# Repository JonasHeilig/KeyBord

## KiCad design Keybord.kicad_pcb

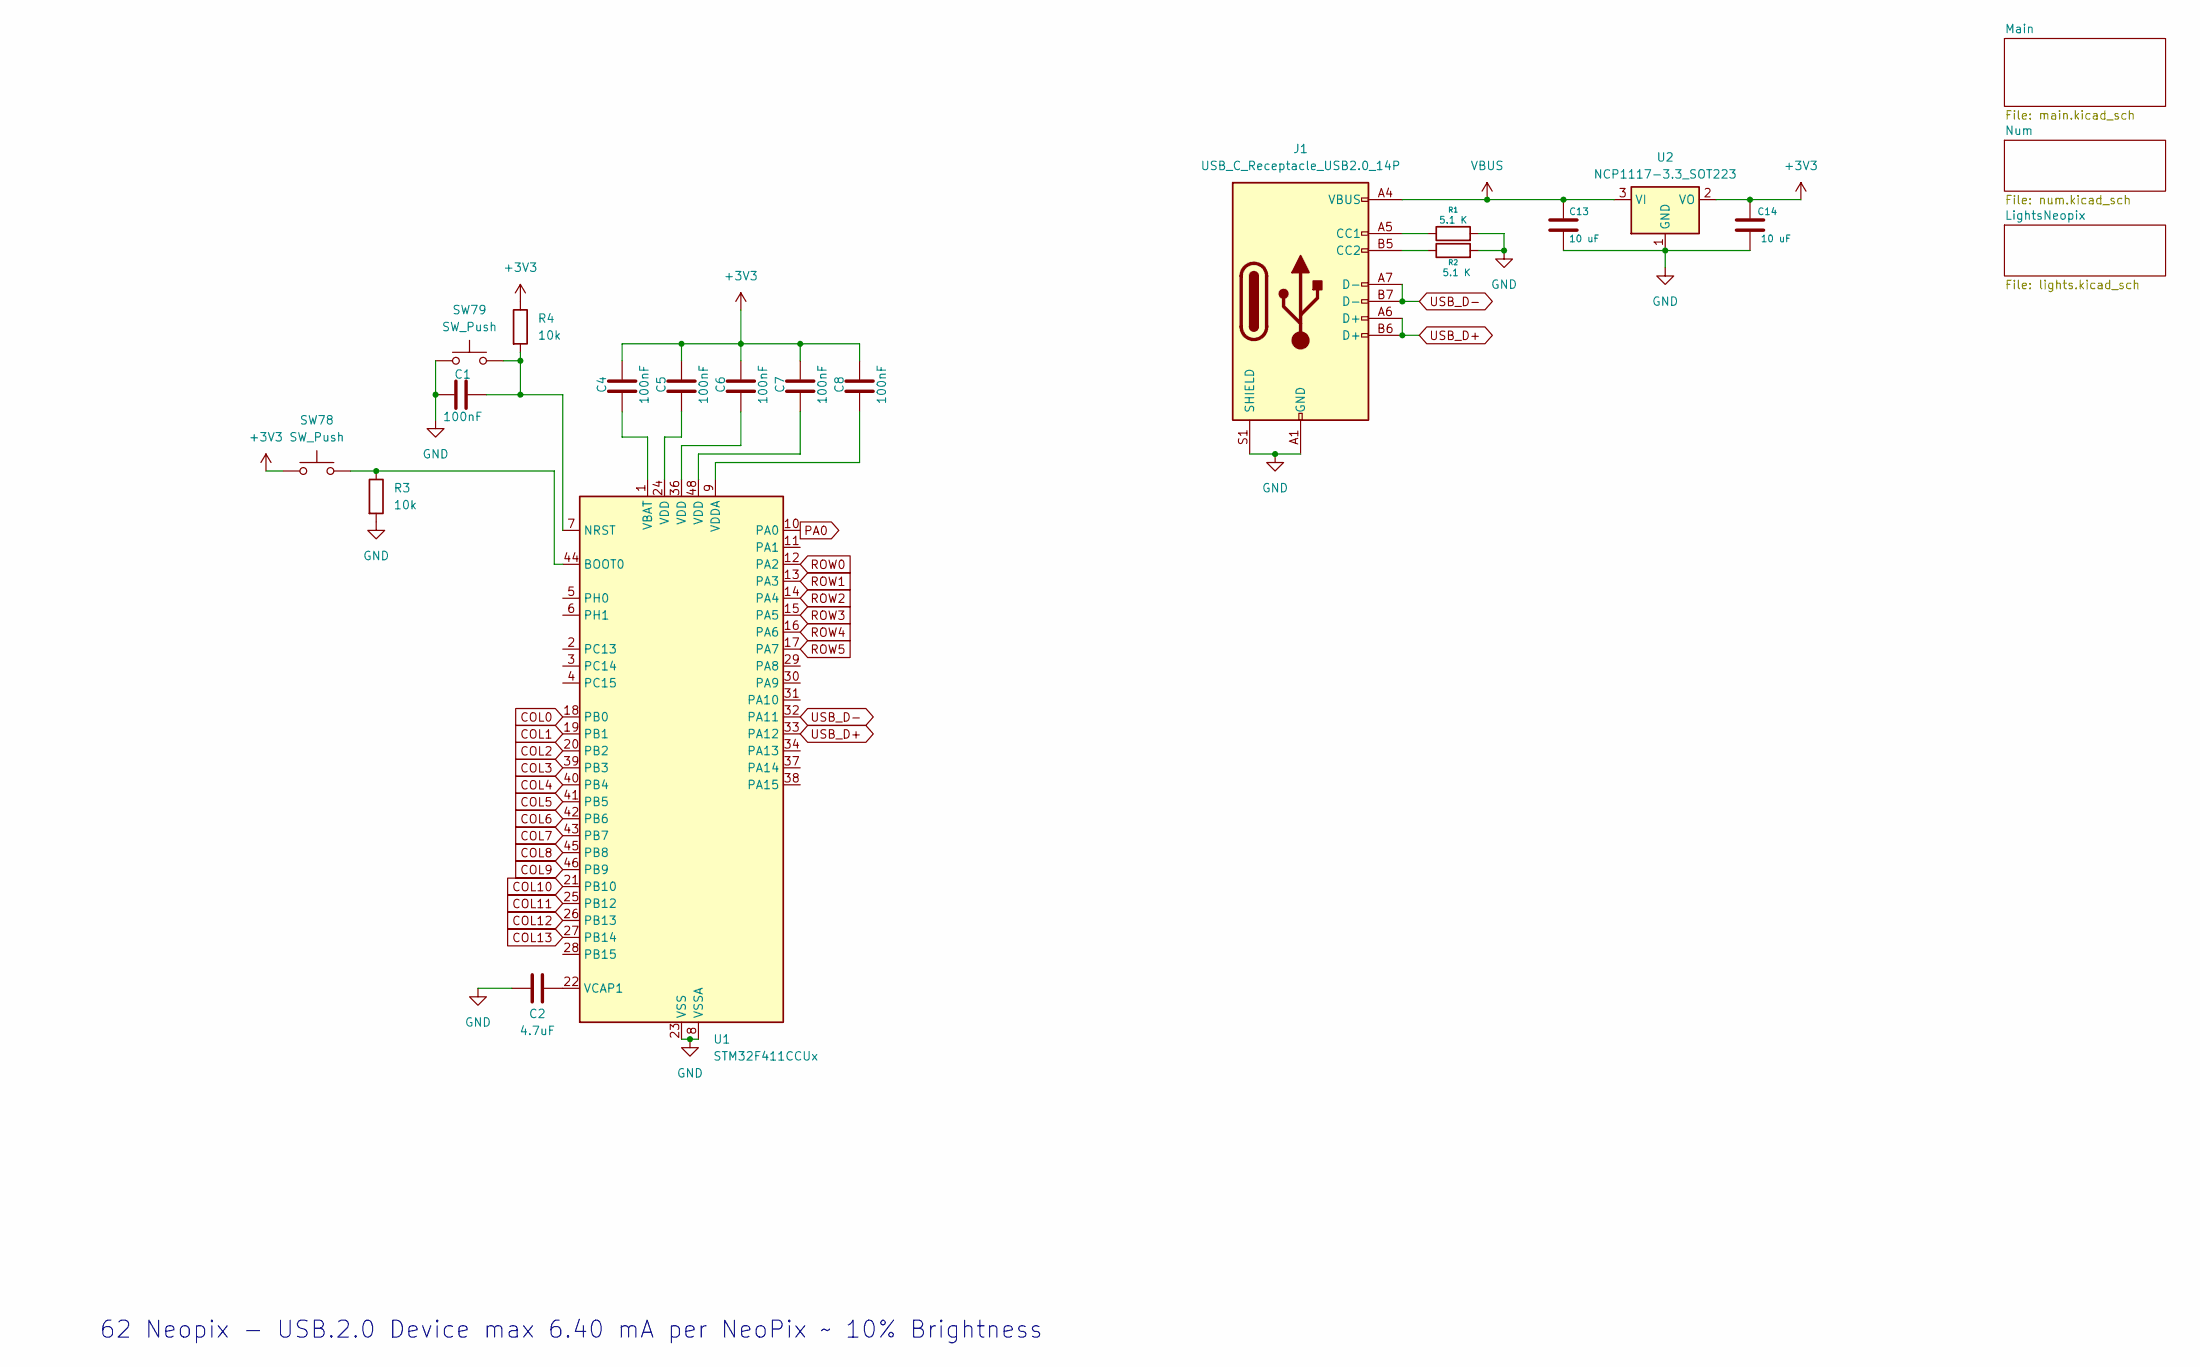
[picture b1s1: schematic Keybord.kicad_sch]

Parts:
C1, C4, C5, C6, C7, C8: 100nF; C_0603_1608Metric
C2: 4.7uF; C_0805_2012Metric
C13, C14: 10 uF; C_0805_2012Metric
J1: USB_C_Receptacle_USB2.0_14P; USB_C_Receptacle_HRO_TYPE-C-31-M-12
R1, R2: 5.1 K; R_0402_1005Metric
R3, R4: 10k; R_0603_1608Metric
SW78, SW79: SW_Push; smd_switch_sunrom4388
U1: STM32F411CCUx; QFN-48-1EP_7x7mm_P0.5mm_EP5.6x5.6mm
U2: NCP1117-3.3_SOT223; SOT-223-3_TabPin2

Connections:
+3V3: C4.2, C5.2, C6.2, C7.2, C8.2, C14.1, R4.1, SW78.1, U2.2 (VO)
COL0: U1.18 (PB0); also elsewhere on the board
COL1: U1.19 (PB1); also elsewhere on the board
COL2: U1.20 (PB2); also elsewhere on the board
COL3: U1.39 (PB3); also elsewhere on the board
COL4: U1.40 (PB4); also elsewhere on the board
COL5: U1.41 (PB5); also elsewhere on the board
COL6: U1.42 (PB6); also elsewhere on the board
COL7: U1.43 (PB7); also elsewhere on the board
COL8: U1.45 (PB8); also elsewhere on the board
COL9: U1.46 (PB9); also elsewhere on the board
COL10: U1.21 (PB10); also elsewhere on the board
COL11: U1.25 (PB12); also elsewhere on the board
COL12: U1.26 (PB13); also elsewhere on the board
COL13: U1.27 (PB14); also elsewhere on the board
GND: C1.1, C2.2, C13.2, C14.2, J1.A1 (GND), J1.A12 (GND), J1.B1 (GND), J1.B12 (GND), J1.S1 (SHIELD), R1.2, R2.2, R3.2, SW79.1, U1.8 (VSSA), U1.23 (VSS), U1.35 (VSS), U1.47 (VSS), U1.49 (VSS), U2.1 (GND); also elsewhere on the board
unnamed: C5.1, U1.24 (VDD)
unnamed: C6.1, U1.36 (VDD)
unnamed: C7.1, U1.48 (VDD)
unnamed: J1.A5 (CC1), R1.1
unnamed: J1.B5 (CC2), R2.1
unnamed: R3.1, SW78.2, U1.44 (BOOT0)
unnamed: C1.2, R4.2, SW79.2, U1.7 (NRST)
unnamed: C4.1, U1.1 (VBAT)
unnamed: C2.1, U1.22 (VCAP1)
unnamed: C8.1, U1.9 (VDDA)
PA0: U1.10 (PA0); also elsewhere on the board
ROW0: U1.12 (PA2); also elsewhere on the board
ROW1: U1.13 (PA3); also elsewhere on the board
ROW2: U1.14 (PA4); also elsewhere on the board
ROW3: U1.15 (PA5); also elsewhere on the board
ROW4: U1.16 (PA6); also elsewhere on the board
ROW5: U1.17 (PA7); also elsewhere on the board
USB_D+: J1.A6 (D+), J1.B6 (D+), U1.33 (PA12)
USB_D-: J1.A7 (D-), J1.B7 (D-), U1.32 (PA11)
VBUS: C13.1, J1.A4 (VBUS), J1.A9 (VBUS), J1.B4 (VBUS), J1.B9 (VBUS), U2.3 (VI); also elsewhere on the board

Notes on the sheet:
62 Neopix - USB.2.0 Device max 6.40 mA per NeoPix ~ 10% Brightness

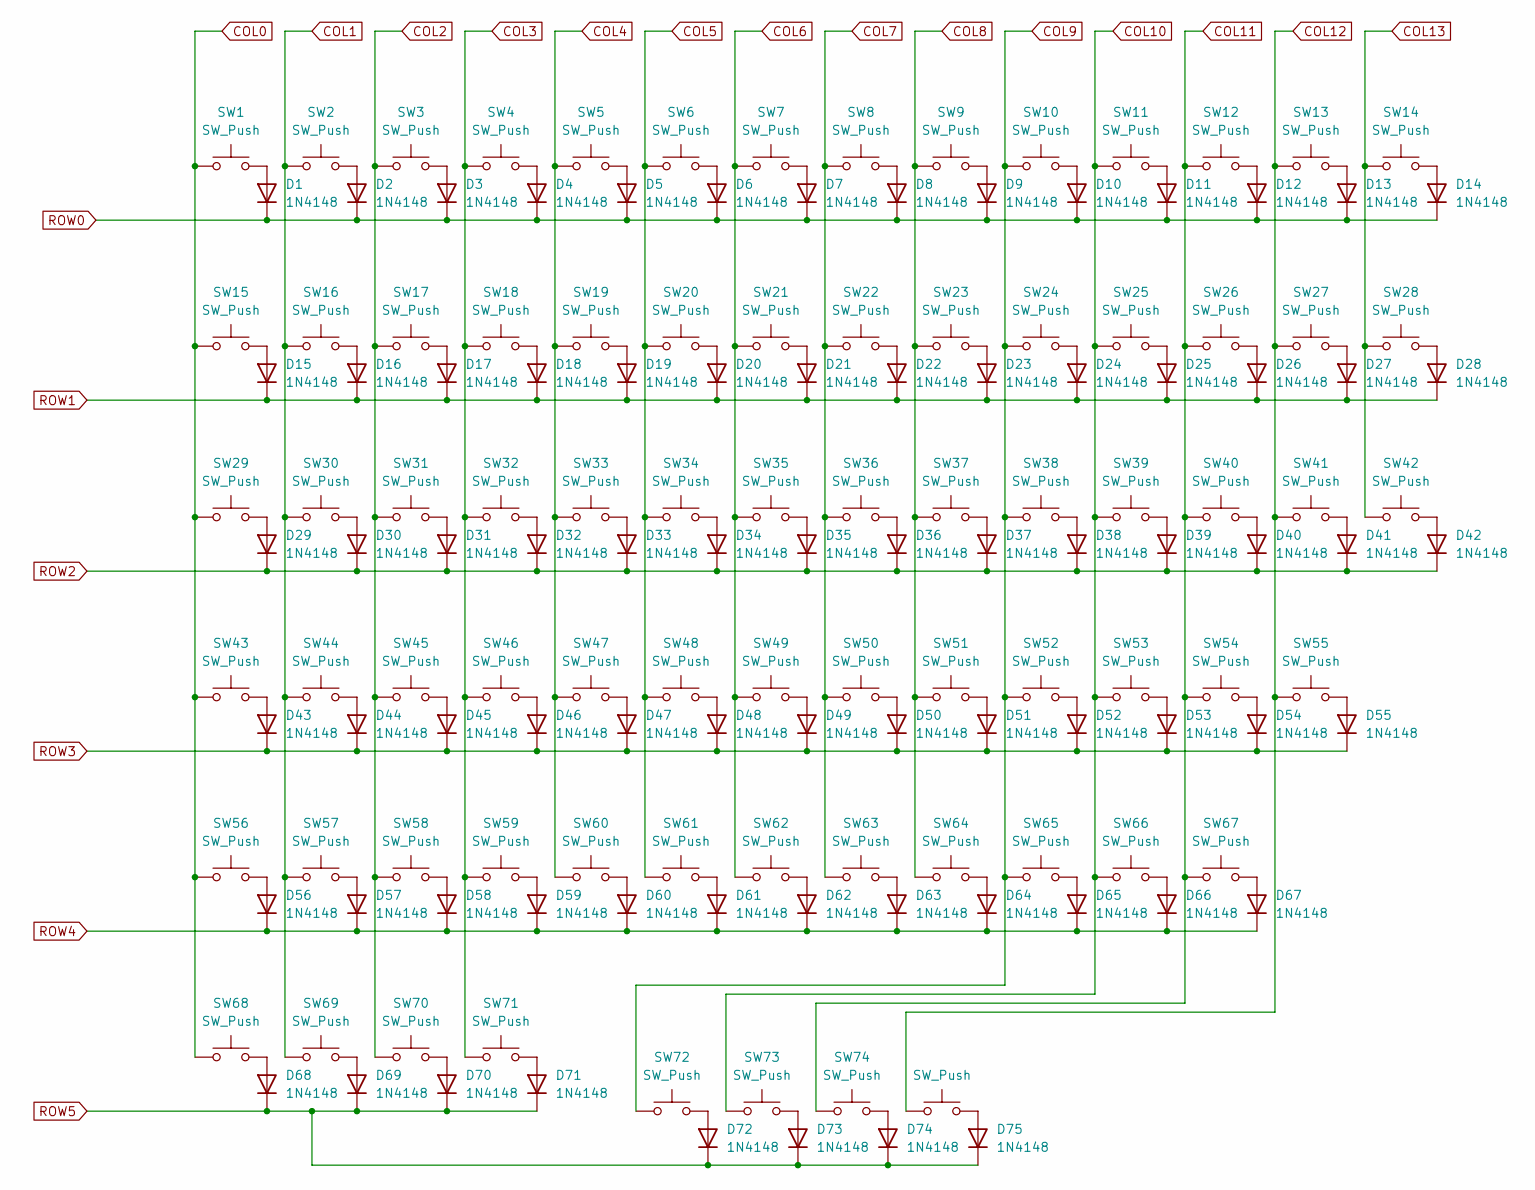
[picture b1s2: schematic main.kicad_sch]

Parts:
D1, D2, D3, D4, D5, D6, D7, D8, D9, D10, D11, D12, D13, D14, D15, D16, D17, D18, D19, D20, D21, D22, D23, D24, D25, D26, D27, D28, D29, D30, D31, D32, D33, D34, D35, D36, D37, D38, D39, D40, D41, D42, D43, D44, D45, D46, D47, D48, D49, D50, D51, D52, D53, D54, D55, D56, D57, D58, D59, D60, D61, D62, D63, D64, D65, D66, D67, D68, D69, D70, D71, D72, D73, D74, D75: 1N4148; D_SOD-123
SW1, SW2, SW3, SW4, SW5, SW6, SW7, SW8, SW9, SW10, SW11, SW12, SW13, SW14, SW15, SW16, SW17, SW18, SW19, SW20, SW21, SW22, SW23, SW24, SW25, SW26, SW27, SW28, SW29, SW30, SW31, SW32, SW33, SW34, SW35, SW36, SW37, SW38, SW39, SW40, SW41, SW42, SW43, SW44, SW45, SW46, SW47, SW48, SW49, SW50, SW51, SW52, SW53, SW54, SW55, SW56, SW57, SW58, SW59, SW60, SW61, SW62, SW63, SW64, SW65, SW66, SW67, SW68, SW69, SW70, SW71, SW72, SW73, SW74, SW75: SW_Push; MX100H

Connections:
COL0: SW1.1, SW15.1, SW29.1, SW43.1, SW56.1, SW68.1; also elsewhere on the board
COL1: SW2.1, SW16.1, SW30.1, SW44.1, SW57.1, SW69.1; also elsewhere on the board
COL2: SW3.1, SW17.1, SW31.1, SW45.1, SW58.1, SW70.1; also elsewhere on the board
COL3: SW4.1, SW18.1, SW32.1, SW46.1, SW59.1, SW71.1; also elsewhere on the board
COL4: SW5.1, SW19.1, SW33.1, SW47.1, SW60.1; also elsewhere on the board
COL5: SW6.1, SW20.1, SW34.1, SW48.1, SW61.1; also elsewhere on the board
COL6: SW7.1, SW21.1, SW35.1, SW49.1, SW62.1; also elsewhere on the board
COL7: SW8.1, SW22.1, SW36.1, SW50.1, SW63.1; also elsewhere on the board
COL8: SW9.1, SW23.1, SW37.1, SW51.1, SW64.1; also elsewhere on the board
COL9: SW10.1, SW24.1, SW38.1, SW52.1, SW65.1, SW72.1; also elsewhere on the board
COL10: SW11.1, SW25.1, SW39.1, SW53.1, SW66.1, SW73.1; also elsewhere on the board
COL11: SW12.1, SW26.1, SW40.1, SW54.1, SW67.1, SW74.1; also elsewhere on the board
COL12: SW13.1, SW27.1, SW41.1, SW55.1, SW75.1; also elsewhere on the board
COL13: SW14.1, SW28.1, SW42.1; also elsewhere on the board
unnamed: D1.2 (A), SW1.2
unnamed: D2.2 (A), SW2.2
unnamed: D3.2 (A), SW3.2
unnamed: D4.2 (A), SW4.2
unnamed: D5.2 (A), SW5.2
unnamed: D6.2 (A), SW6.2
unnamed: D7.2 (A), SW7.2
unnamed: D8.2 (A), SW8.2
unnamed: D9.2 (A), SW9.2
unnamed: D10.2 (A), SW10.2
unnamed: D11.2 (A), SW11.2
unnamed: D12.2 (A), SW12.2
unnamed: D13.2 (A), SW13.2
unnamed: D14.2 (A), SW14.2
unnamed: D15.2 (A), SW15.2
unnamed: D16.2 (A), SW16.2
unnamed: D17.2 (A), SW17.2
unnamed: D18.2 (A), SW18.2
unnamed: D19.2 (A), SW19.2
unnamed: D20.2 (A), SW20.2
unnamed: D21.2 (A), SW21.2
unnamed: D22.2 (A), SW22.2
unnamed: D23.2 (A), SW23.2
unnamed: D24.2 (A), SW24.2
unnamed: D25.2 (A), SW25.2
unnamed: D26.2 (A), SW26.2
unnamed: D27.2 (A), SW27.2
unnamed: D28.2 (A), SW28.2
unnamed: D29.2 (A), SW29.2
unnamed: D30.2 (A), SW30.2
unnamed: D31.2 (A), SW31.2
unnamed: D32.2 (A), SW32.2
unnamed: D33.2 (A), SW33.2
unnamed: D34.2 (A), SW34.2
unnamed: D35.2 (A), SW35.2
unnamed: D36.2 (A), SW36.2
unnamed: D37.2 (A), SW37.2
unnamed: D38.2 (A), SW38.2
unnamed: D39.2 (A), SW39.2
unnamed: D40.2 (A), SW40.2
unnamed: D41.2 (A), SW41.2
unnamed: D42.2 (A), SW42.2
unnamed: D43.2 (A), SW43.2
unnamed: D44.2 (A), SW44.2
unnamed: D45.2 (A), SW45.2
unnamed: D46.2 (A), SW46.2
unnamed: D47.2 (A), SW47.2
unnamed: D48.2 (A), SW48.2
unnamed: D49.2 (A), SW49.2
unnamed: D50.2 (A), SW50.2
unnamed: D51.2 (A), SW51.2
unnamed: D52.2 (A), SW52.2
unnamed: D53.2 (A), SW53.2
unnamed: D54.2 (A), SW54.2
unnamed: D55.2 (A), SW55.2
unnamed: D56.2 (A), SW56.2
unnamed: D57.2 (A), SW57.2
unnamed: D58.2 (A), SW58.2
unnamed: D59.2 (A), SW59.2
unnamed: D60.2 (A), SW60.2
unnamed: D61.2 (A), SW61.2
unnamed: D62.2 (A), SW62.2
unnamed: D63.2 (A), SW63.2
unnamed: D64.2 (A), SW64.2
unnamed: D65.2 (A), SW65.2
unnamed: D66.2 (A), SW66.2
unnamed: D67.2 (A), SW67.2
unnamed: D68.2 (A), SW68.2
unnamed: D69.2 (A), SW69.2
unnamed: D70.2 (A), SW70.2
unnamed: D71.2 (A), SW71.2
unnamed: D72.2 (A), SW72.2
unnamed: D73.2 (A), SW73.2
unnamed: D74.2 (A), SW74.2
unnamed: D75.2 (A), SW75.2
ROW0: D1.1 (K), D2.1 (K), D3.1 (K), D4.1 (K), D5.1 (K), D6.1 (K), D7.1 (K), D8.1 (K), D9.1 (K), D10.1 (K), D11.1 (K), D12.1 (K), D13.1 (K), D14.1 (K); also elsewhere on the board
ROW1: D15.1 (K), D16.1 (K), D17.1 (K), D18.1 (K), D19.1 (K), D20.1 (K), D21.1 (K), D22.1 (K), D23.1 (K), D24.1 (K), D25.1 (K), D26.1 (K), D27.1 (K), D28.1 (K); also elsewhere on the board
ROW2: D29.1 (K), D30.1 (K), D31.1 (K), D32.1 (K), D33.1 (K), D34.1 (K), D35.1 (K), D36.1 (K), D37.1 (K), D38.1 (K), D39.1 (K), D40.1 (K), D41.1 (K), D42.1 (K); also elsewhere on the board
ROW3: D43.1 (K), D44.1 (K), D45.1 (K), D46.1 (K), D47.1 (K), D48.1 (K), D49.1 (K), D50.1 (K), D51.1 (K), D52.1 (K), D53.1 (K), D54.1 (K), D55.1 (K); also elsewhere on the board
ROW4: D56.1 (K), D57.1 (K), D58.1 (K), D59.1 (K), D60.1 (K), D61.1 (K), D62.1 (K), D63.1 (K), D64.1 (K), D65.1 (K), D66.1 (K), D67.1 (K); also elsewhere on the board
ROW5: D68.1 (K), D69.1 (K), D70.1 (K), D71.1 (K), D72.1 (K), D73.1 (K), D74.1 (K), D75.1 (K); also elsewhere on the board

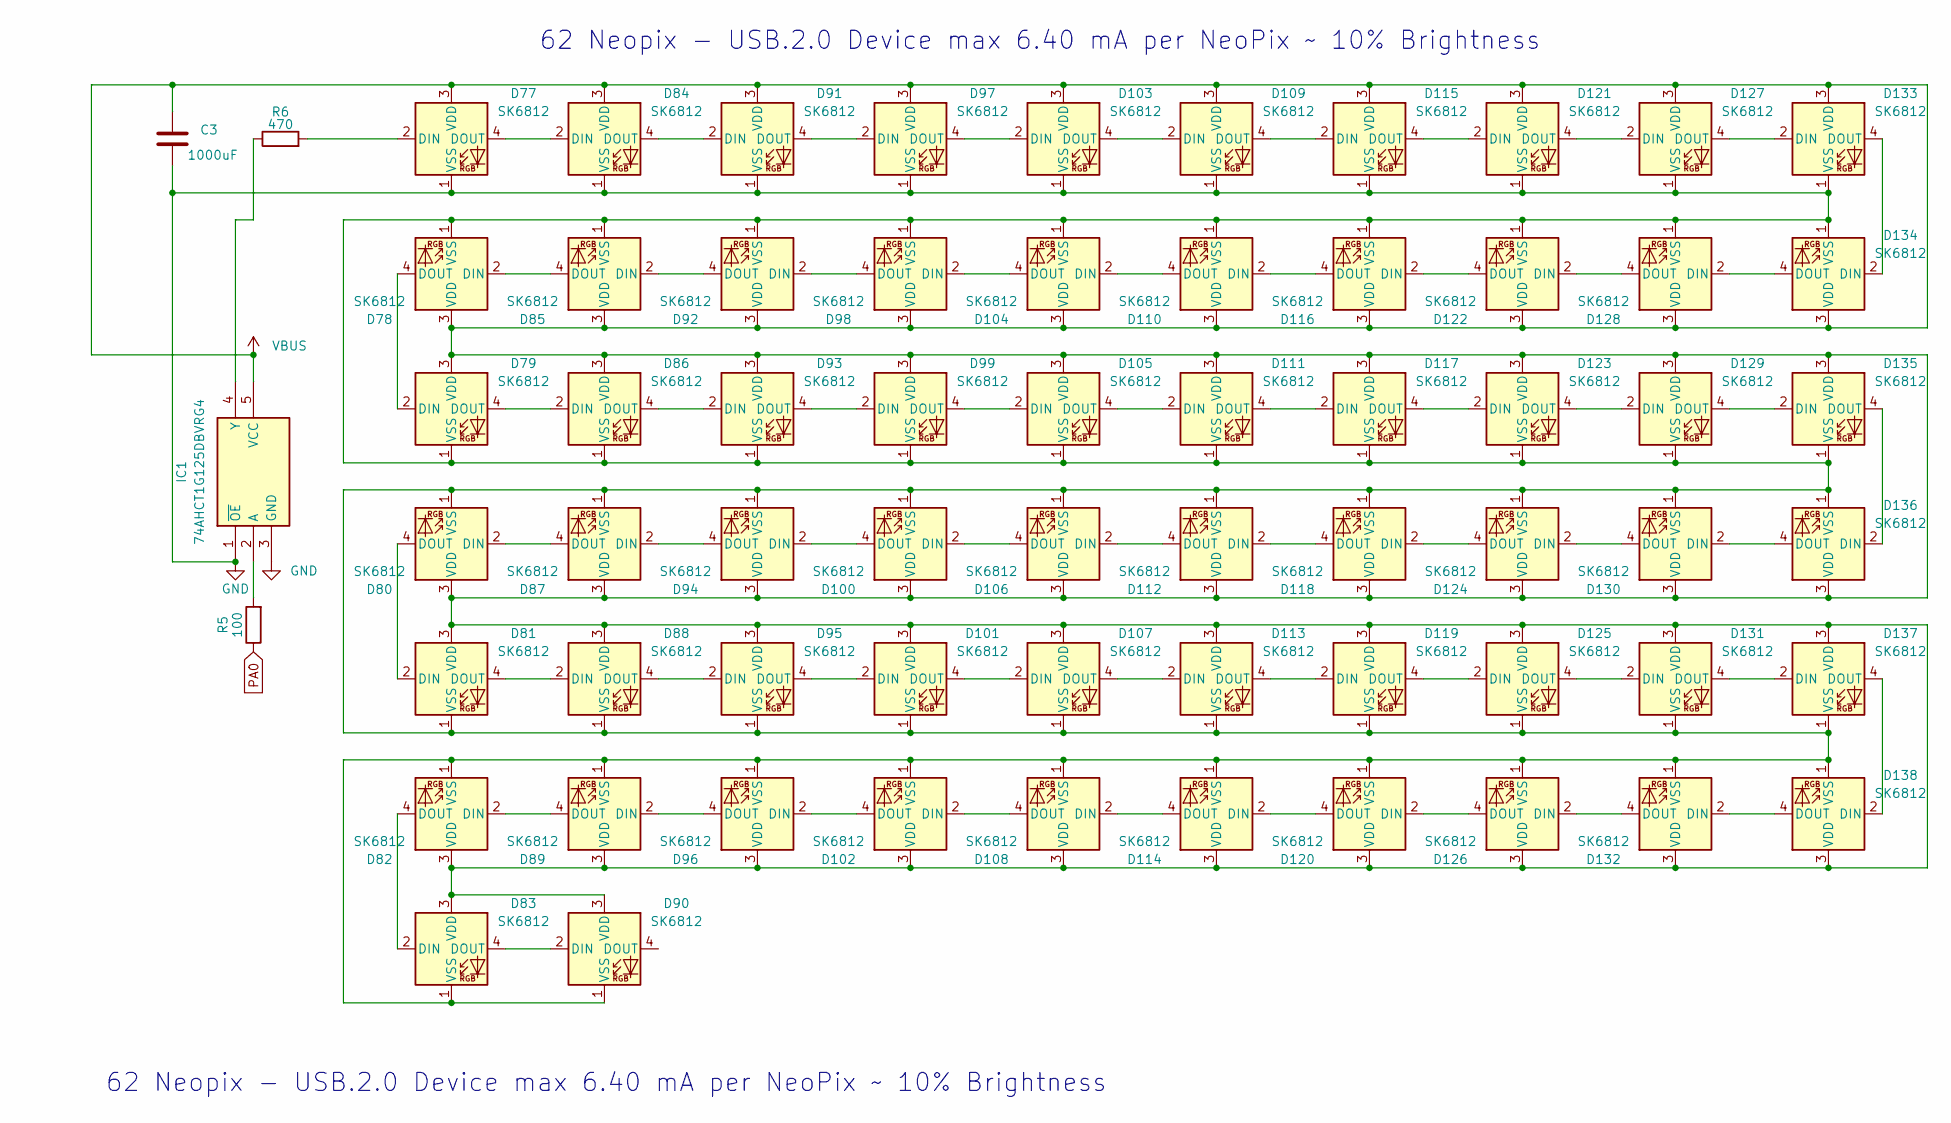
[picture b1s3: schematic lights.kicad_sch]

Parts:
C3: 1000uF; C_Rect_L4.0mm_W2.5mm_P2.50mm
D77, D78, D79, D80, D81, D82, D83, D84, D85, D86, D87, D88, D89, D90, D91, D92, D93, D94, D95, D96, D97, D98, D99, D100, D101, D102, D103, D104, D105, D106, D107, D108, D109, D110, D111, D112, D113, D114, D115, D116, D117, D118, D119, D120, D121, D122, D123, D124, D125, D126, D127, D128, D129, D130, D131, D132, D133, D134, D135, D136, D137, D138: SK6812; LED_SK6812_PLCC4_5.0x5.0mm_P3.2mm
IC1: 74AHCT1G125DBVRG4; SOT95P280X145-5N; Mouser Part Number 595-74AHCT1G125DBVRG
R5: 100; R_0603_1608Metric
R6: 470; R_0603_1608Metric

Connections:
GND: C3.2, D77.1 (VSS), D78.1 (VSS), D79.1 (VSS), D80.1 (VSS), D81.1 (VSS), D82.1 (VSS), D83.1 (VSS), D84.1 (VSS), D85.1 (VSS), D86.1 (VSS), D87.1 (VSS), D88.1 (VSS), D89.1 (VSS), D90.1 (VSS), D91.1 (VSS), D92.1 (VSS), D93.1 (VSS), D94.1 (VSS), D95.1 (VSS), D96.1 (VSS), D97.1 (VSS), D98.1 (VSS), D99.1 (VSS), D100.1 (VSS), D101.1 (VSS), D102.1 (VSS), D103.1 (VSS), D104.1 (VSS), D105.1 (VSS), D106.1 (VSS), D107.1 (VSS), D108.1 (VSS), D109.1 (VSS), D110.1 (VSS), D111.1 (VSS), D112.1 (VSS), D113.1 (VSS), D114.1 (VSS), D115.1 (VSS), D116.1 (VSS), D117.1 (VSS), D118.1 (VSS), D119.1 (VSS), D120.1 (VSS), D121.1 (VSS), D122.1 (VSS), D123.1 (VSS), D124.1 (VSS), D125.1 (VSS), D126.1 (VSS), D127.1 (VSS), D128.1 (VSS), D129.1 (VSS), D130.1 (VSS), D131.1 (VSS), D132.1 (VSS), D133.1 (VSS), D134.1 (VSS), D135.1 (VSS), D136.1 (VSS), D137.1 (VSS), D138.1 (VSS), IC1.1 (~OE), IC1.3 (GND); also elsewhere on the board
unnamed: D77.2 (DIN), R6.2
unnamed: D77.4 (DOUT), D84.2 (DIN)
unnamed: D78.2 (DIN), D85.4 (DOUT)
unnamed: D78.4 (DOUT), D79.2 (DIN)
unnamed: D79.4 (DOUT), D86.2 (DIN)
unnamed: D80.2 (DIN), D87.4 (DOUT)
unnamed: D80.4 (DOUT), D81.2 (DIN)
unnamed: D81.4 (DOUT), D88.2 (DIN)
unnamed: D82.2 (DIN), D89.4 (DOUT)
unnamed: D82.4 (DOUT), D83.2 (DIN)
unnamed: D83.4 (DOUT), D90.2 (DIN)
unnamed: D84.4 (DOUT), D91.2 (DIN)
unnamed: D85.2 (DIN), D92.4 (DOUT)
unnamed: D86.4 (DOUT), D93.2 (DIN)
unnamed: D87.2 (DIN), D94.4 (DOUT)
unnamed: D88.4 (DOUT), D95.2 (DIN)
unnamed: D89.2 (DIN), D96.4 (DOUT)
unnamed: D91.4 (DOUT), D97.2 (DIN)
unnamed: D92.2 (DIN), D98.4 (DOUT)
unnamed: D93.4 (DOUT), D99.2 (DIN)
unnamed: D100.2 (DIN), D106.4 (DOUT)
unnamed: D94.2 (DIN), D100.4 (DOUT)
unnamed: D95.4 (DOUT), D101.2 (DIN)
unnamed: D101.4 (DOUT), D107.2 (DIN)
unnamed: D102.2 (DIN), D108.4 (DOUT)
unnamed: D96.2 (DIN), D102.4 (DOUT)
unnamed: D97.4 (DOUT), D103.2 (DIN)
unnamed: D103.4 (DOUT), D109.2 (DIN)
unnamed: D104.2 (DIN), D110.4 (DOUT)
unnamed: D98.2 (DIN), D104.4 (DOUT)
unnamed: D99.4 (DOUT), D105.2 (DIN)
unnamed: D105.4 (DOUT), D111.2 (DIN)
unnamed: D106.2 (DIN), D112.4 (DOUT)
unnamed: D107.4 (DOUT), D113.2 (DIN)
unnamed: D108.2 (DIN), D114.4 (DOUT)
unnamed: D109.4 (DOUT), D115.2 (DIN)
unnamed: D110.2 (DIN), D116.4 (DOUT)
unnamed: D111.4 (DOUT), D117.2 (DIN)
unnamed: D112.2 (DIN), D118.4 (DOUT)
unnamed: D113.4 (DOUT), D119.2 (DIN)
unnamed: D114.2 (DIN), D120.4 (DOUT)
unnamed: D115.4 (DOUT), D121.2 (DIN)
unnamed: D116.2 (DIN), D122.4 (DOUT)
unnamed: D117.4 (DOUT), D123.2 (DIN)
unnamed: D118.2 (DIN), D124.4 (DOUT)
unnamed: D119.4 (DOUT), D125.2 (DIN)
unnamed: D120.2 (DIN), D126.4 (DOUT)
unnamed: D121.4 (DOUT), D127.2 (DIN)
unnamed: D122.2 (DIN), D128.4 (DOUT)
unnamed: D123.4 (DOUT), D129.2 (DIN)
unnamed: D124.2 (DIN), D130.4 (DOUT)
unnamed: D125.4 (DOUT), D131.2 (DIN)
unnamed: D126.2 (DIN), D132.4 (DOUT)
unnamed: D127.4 (DOUT), D133.2 (DIN)
unnamed: D128.2 (DIN), D134.4 (DOUT)
unnamed: D129.4 (DOUT), D135.2 (DIN)
unnamed: D130.2 (DIN), D136.4 (DOUT)
unnamed: D131.4 (DOUT), D137.2 (DIN)
unnamed: D132.2 (DIN), D138.4 (DOUT)
unnamed: D133.4 (DOUT), D134.2 (DIN)
unnamed: D135.4 (DOUT), D136.2 (DIN)
unnamed: D137.4 (DOUT), D138.2 (DIN)
unnamed: IC1.2 (A), R5.2
unnamed: IC1.4 (Y), R6.1
PA0: R5.1; also elsewhere on the board
VBUS: C3.1, D77.3 (VDD), D78.3 (VDD), D79.3 (VDD), D80.3 (VDD), D81.3 (VDD), D82.3 (VDD), D83.3 (VDD), D84.3 (VDD), D85.3 (VDD), D86.3 (VDD), D87.3 (VDD), D88.3 (VDD), D89.3 (VDD), D90.3 (VDD), D91.3 (VDD), D92.3 (VDD), D93.3 (VDD), D94.3 (VDD), D95.3 (VDD), D96.3 (VDD), D97.3 (VDD), D98.3 (VDD), D99.3 (VDD), D100.3 (VDD), D101.3 (VDD), D102.3 (VDD), D103.3 (VDD), D104.3 (VDD), D105.3 (VDD), D106.3 (VDD), D107.3 (VDD), D108.3 (VDD), D109.3 (VDD), D110.3 (VDD), D111.3 (VDD), D112.3 (VDD), D113.3 (VDD), D114.3 (VDD), D115.3 (VDD), D116.3 (VDD), D117.3 (VDD), D118.3 (VDD), D119.3 (VDD), D120.3 (VDD), D121.3 (VDD), D122.3 (VDD), D123.3 (VDD), D124.3 (VDD), D125.3 (VDD), D126.3 (VDD), D127.3 (VDD), D128.3 (VDD), D129.3 (VDD), D130.3 (VDD), D131.3 (VDD), D132.3 (VDD), D133.3 (VDD), D134.3 (VDD), D135.3 (VDD), D136.3 (VDD), D137.3 (VDD), D138.3 (VDD), IC1.5 (VCC); also elsewhere on the board

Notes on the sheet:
62 Neopix - USB.2.0 Device max 6.40 mA per NeoPix ~ 10% Brightness

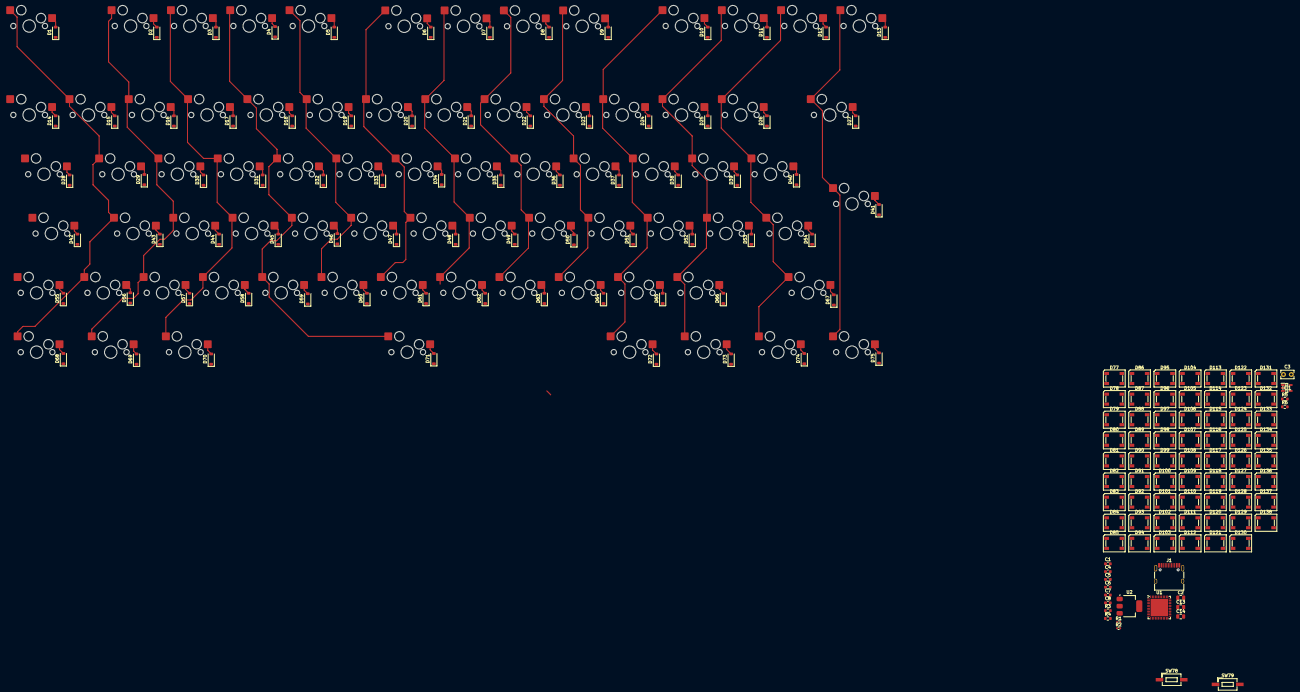
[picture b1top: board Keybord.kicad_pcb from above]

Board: 2 copper layers, 234 parts (0 on the bottom side), 175 nets.

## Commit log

2025-10-25 Keymatrix
2025-10-26 Add Neopix
2025-10-26 Finalilize the Keybord Shematic
2025-10-26 Start to fix ERC
2025-10-27 Fixing. Add Footprints
2025-10-27 Switch Layout on PCB
2025-10-28 Fix routing on Shematic, PCB Diode Place, ROW routing
